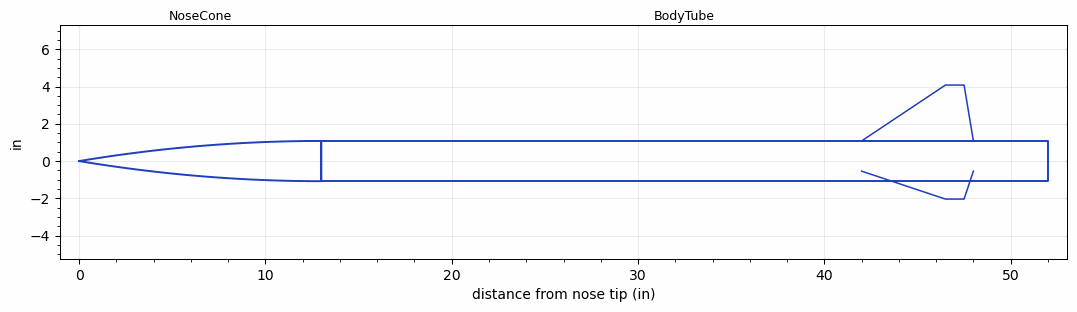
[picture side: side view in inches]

<RASAeroDocument>
 <FileVersion>2</FileVersion>
 <RocketDesign>
  <NoseCone>
   <Length>13</Length>
   <Diameter>2.16</Diameter>
   <Shape>Parabolic</Shape>
   <Location>0</Location>
  </NoseCone>
  <BodyTube>
   <Length>39</Length>
   <Diameter>2.16</Diameter>
   <Location>13</Location>
   <Fin>
    <Count>3</Count>
    <Chord>6</Chord>
    <Span>3</Span>
    <SweepDistance>4.5</SweepDistance>
    <TipChord>1</TipChord>
    <Thickness>0.07</Thickness>
    <Location>10</Location>
    <AirfoilSection>Rounded</AirfoilSection>
   </Fin>
  </BodyTube>
  <Surface>Galvanized Metal</Surface>
  <ModifiedBarrowman>True</ModifiedBarrowman>
  <Turbulence>False</Turbulence>
  <UseBooster1>False</UseBooster1>
  <UseBooster2>False</UseBooster2>
 </RocketDesign>
 <LaunchSite>
  <Altitude>253</Altitude>
  <Pressure>0</Pressure>
  <RodAngle>0</RodAngle>
  <RodLength>8</RodLength>
  <Temperature>65</Temperature>
  <WindSpeed>0</WindSpeed>
 </LaunchSite>
 <Recovery>
  <Altitude1>1000</Altitude1>
  <Altitude2>1500</Altitude2>
  <DeviceType1>Parachute</DeviceType1>
  <DeviceType2>Parachute</DeviceType2>
  <Event1>True</Event1>
  <Event2>True</Event2>
  <Size1>30.57</Size1>
  <Size2>96</Size2>
  <EventType1>Apogee</EventType1>
  <EventType2>Altitude</EventType2>
  <CD1>0.75</CD1>
  <CD2>2.2</CD2>
 </Recovery>
 <SimulationList>
  <Simulation>
   <SustainerEngine>J1999N  (AT)</SustainerEngine>
   <SustainerLaunchWt>5.34</SustainerLaunchWt>
   <SustainerNozzleDiameter>0.5</SustainerNozzleDiameter>
   <SustainerCG>35.7</SustainerCG>
   <SustainerIgnitionDelay>0</SustainerIgnitionDelay>
   <Booster1SeparationDelay>0</Booster1SeparationDelay>
   <Booster1IgnitionDelay>0</Booster1IgnitionDelay>
   <IncludeBooster1>False</IncludeBooster1>
   <Booster2Delay>0</Booster2Delay>
   <IncludeBooster2>False</IncludeBooster2>
   <TimetoApogee>23.33044</TimetoApogee>
   <MaxAltitude>12272.14</MaxAltitude>
   <MaxVelocity>1806.933</MaxVelocity>
  </Simulation>
  <Simulation>
   <SustainerEngine>J1799N  (AT)</SustainerEngine>
   <SustainerLaunchWt>6.37</SustainerLaunchWt>
   <SustainerCG>31.8</SustainerCG>
   <SustainerIgnitionDelay>0</SustainerIgnitionDelay>
   <Booster1SeparationDelay>0</Booster1SeparationDelay>
   <Booster1IgnitionDelay>0</Booster1IgnitionDelay>
   <IncludeBooster1>False</IncludeBooster1>
   <Booster2Delay>0</Booster2Delay>
   <IncludeBooster2>False</IncludeBooster2>
   <TimetoApogee>22.82043</TimetoApogee>
   <MaxAltitude>10548</MaxAltitude>
   <MaxVelocity>1304.797</MaxVelocity>
  </Simulation>
 </SimulationList>
</RASAeroDocument>
